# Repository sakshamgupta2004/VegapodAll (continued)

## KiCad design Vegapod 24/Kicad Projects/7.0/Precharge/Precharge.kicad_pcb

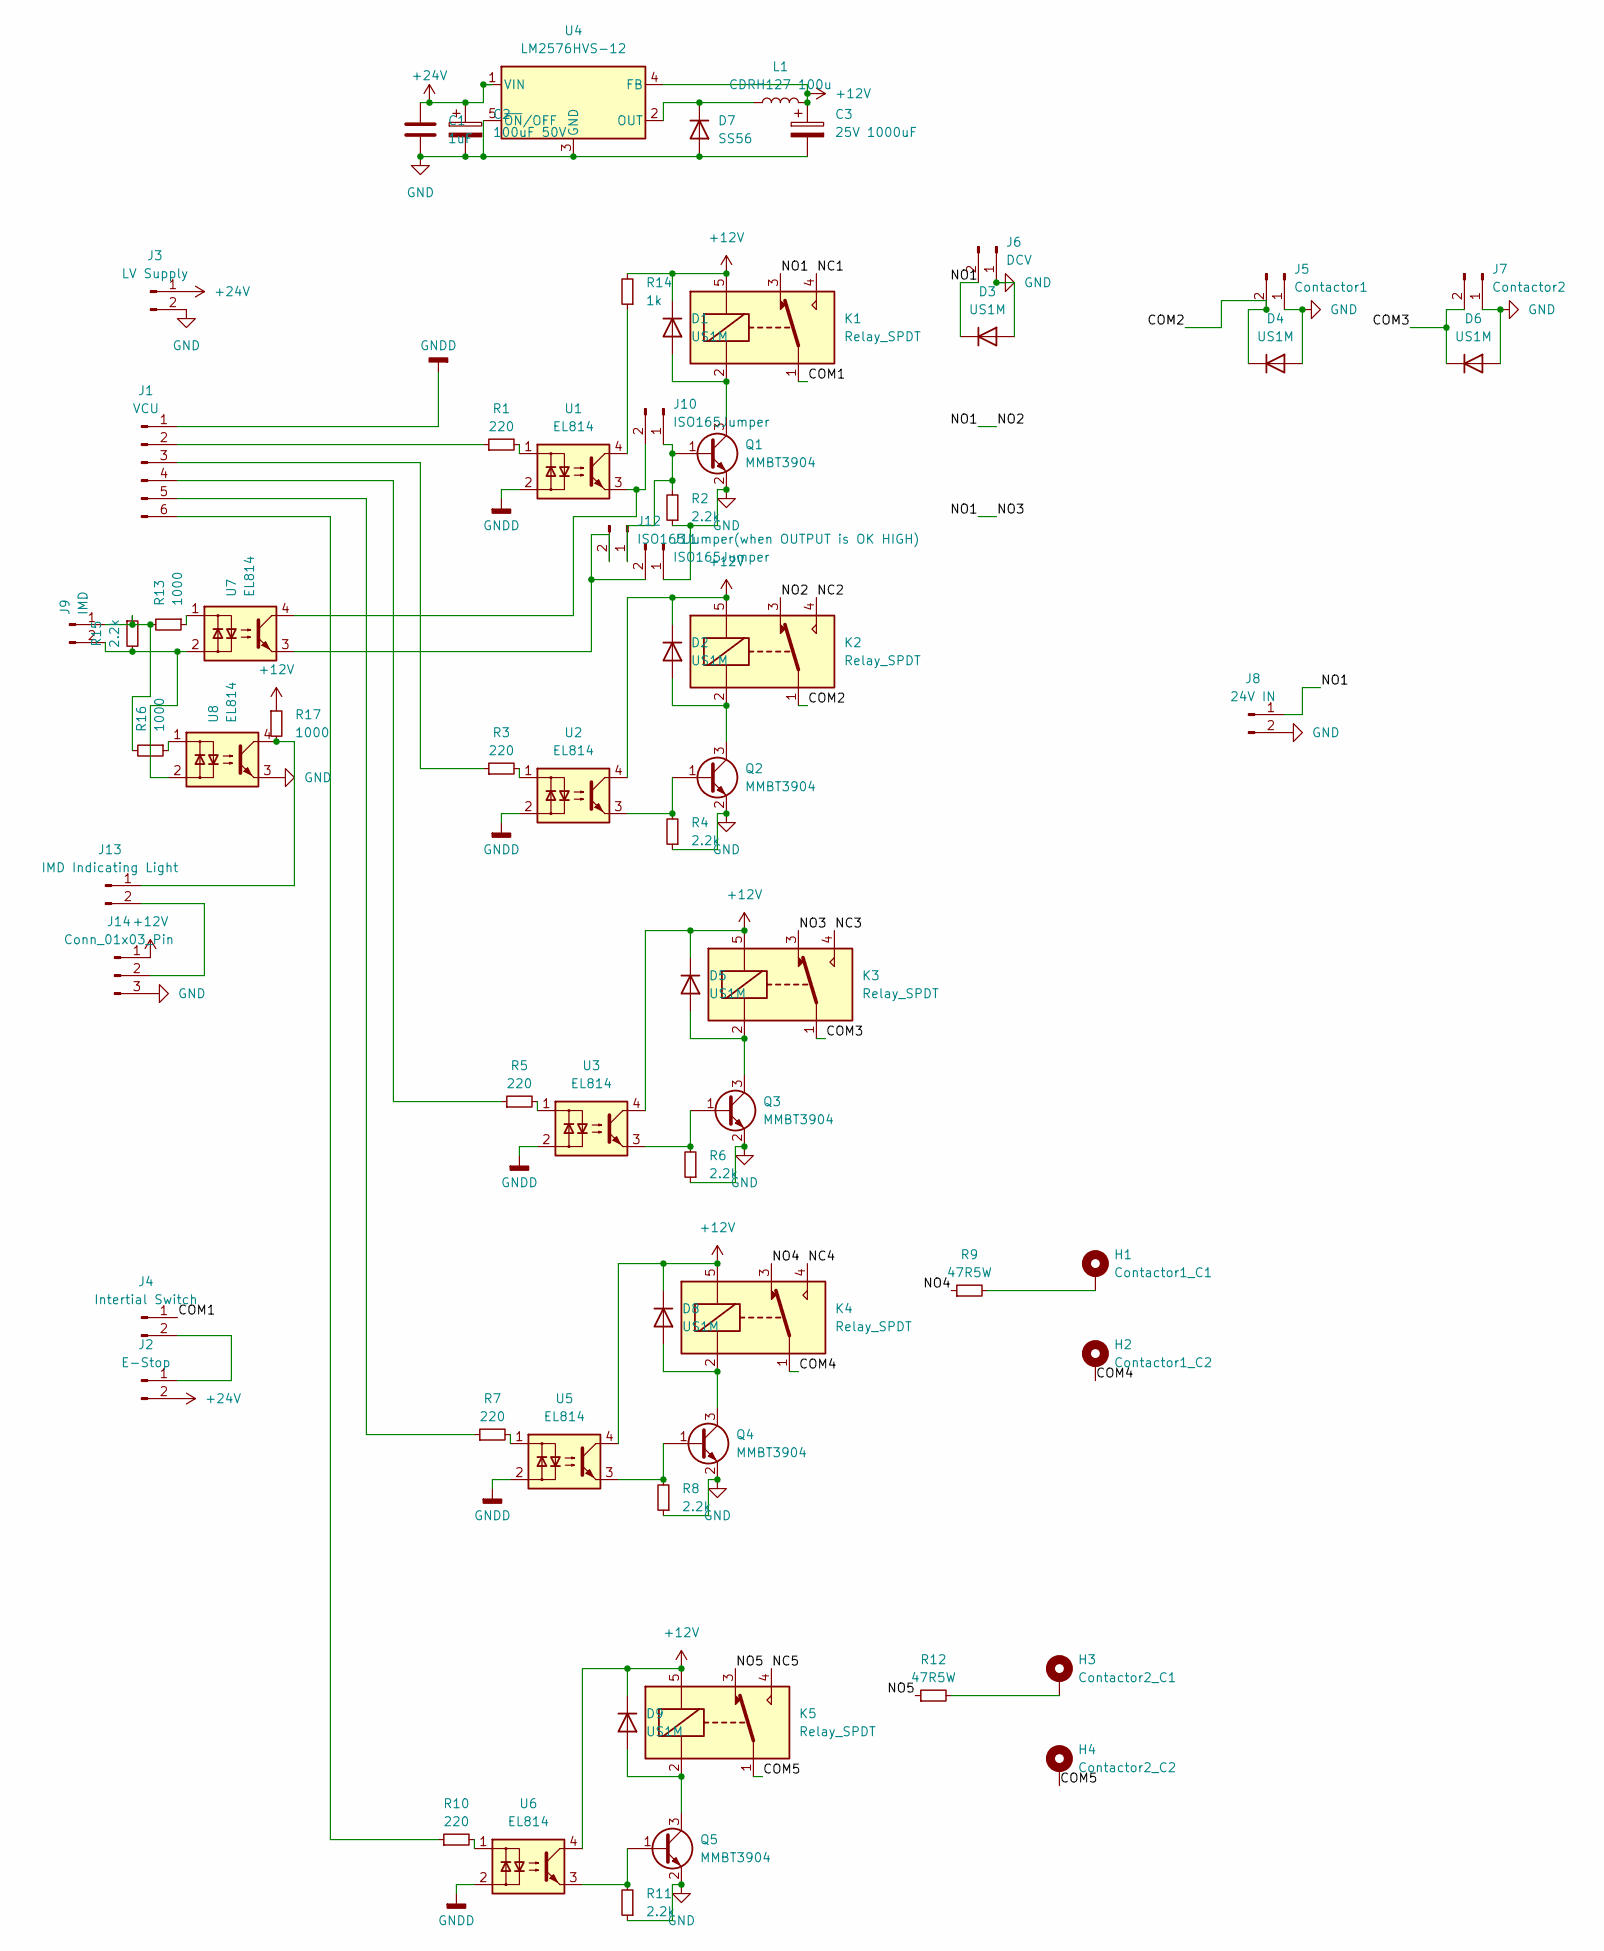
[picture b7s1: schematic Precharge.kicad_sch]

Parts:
C1: 1uF; C_1206_3216Metric_Pad1.33x1.80mm_HandSolder
C2: 100uF 50V; CP_Elec_8x10.5
C3: 25V 1000uF; CP_Elec_10x12.5
D1, D2, D3, D4, D5, D6, D8, D9: US1M; D_SMA-SMB_Universal_Handsoldering
D7: SS56; D_SMA-SMB_Universal_Handsoldering
H1: Contactor1_C1; MountingHole_6.4mm_M6_DIN965_Pad
H2: Contactor1_C2; MountingHole_6.4mm_M6_DIN965_Pad
H3: Contactor2_C1; MountingHole_6.4mm_M6_DIN965_Pad
H4: Contactor2_C2; MountingHole_6.4mm_M6_DIN965_Pad
J1: VCU; JST_XH_B6B-XH-A_1x06_P2.50mm_Vertical
J2: E-Stop; PhoenixContact_MCV_1,5_2-G-5.08_1x02_P5.08mm_Vertical
J3: LV Supply; PhoenixContact_MCV_1,5_2-G-5.08_1x02_P5.08mm_Vertical
J4: Intertial Switch; PhoenixContact_MCV_1,5_2-G-5.08_1x02_P5.08mm_Vertical
J5: Contactor1; PinHeader_1x02_P2.54mm_Vertical
J6: DCV; PhoenixContact_MCV_1,5_2-G-5.08_1x02_P5.08mm_Vertical
J7: Contactor2; PinHeader_1x02_P2.54mm_Vertical
J8: 24V IN; PinHeader_1x02_P2.54mm_Vertical
J9: IMD; PinHeader_1x02_P2.54mm_Vertical
J10, J11: ISO165Jumper; PinHeader_1x02_P1.27mm_Vertical
J12: ISO165Jumper(when OUTPUT is OK HIGH); PinHeader_1x02_P1.27mm_Vertical
J13: IMD Indicating Light; PhoenixContact_MCV_1,5_2-G-5.08_1x02_P5.08mm_Vertical
J14: Conn_01x03_Pin; PinHeader_1x03_P1.27mm_Vertical
K1, K2, K3, K4, K5: Relay_SPDT; Relay_SPDT_Omron-G5LE-1
L1: CDRH127 100u; L_12x12mm_H8mm
Q1, Q2, Q3, Q4, Q5: MMBT3904; SOT-23_Handsoldering
R1, R3, R5, R7, R10: 220; R_0805_2012Metric_Pad1.20x1.40mm_HandSolder
R2, R4, R6, R8, R11, R15: 2.2k; R_0805_2012Metric_Pad1.20x1.40mm_HandSolder
R9, R12: 47R5W; R_Axial_DIN0617_L17.0mm_D6.0mm_P7.62mm_Vertical
R13, R16, R17: 1000; R_0805_2012Metric_Pad1.20x1.40mm_HandSolder
R14: 1k; R_0805_2012Metric_Pad1.20x1.40mm_HandSolder
U1, U2, U3, U5, U6, U7, U8: EL814; SMDIP-4_W9.53mm
U4: LM2576HVS-12; TO-263-5_TabPin3

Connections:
+12V: C3.1, D1.1 (K), D2.1 (K), D5.1 (K), D8.1 (K), D9.1 (K), J14.1, K1.5, K2.5, K3.5, K4.5, K5.5, L1.2, R14.2, R17.1, U2.4, U3.4, U4.4 (FB), U5.4, U6.4
+24V: C1.1, C2.1, J2.2, J3.1, U4.1 (VIN)
/COM1: J4.1, K1.1
/COM2: D4.1 (K), J5.2, K2.1
/COM3: D6.1 (K), J7.2, K3.1
/COM4: H2.1, K4.1
/COM5: H4.1, K5.1
/NC1: K1.4
/NC2: K2.4
/NC3: K3.4
/NC4: K4.4
/NC5: K5.4
/NO1: D3.1 (K), J6.2, J8.1, K1.3, K2.3, K3.3
/NO4: K4.3, R9.1
/NO5: K5.3, R12.1
GND: C1.2, C2.2, C3.2, D3.2 (A), D4.2 (A), D6.2 (A), D7.2 (A), J3.2, J5.1, J6.1, J7.1, J8.2, J11.1, J14.3, Q1.2 (E), Q2.2 (E), Q3.2 (E), Q4.2 (E), Q5.2 (E), R2.1, R4.1, R6.1, R8.1, R11.1, U4.3 (GND), U4.5 (~ON/OFF), U8.3
GNDD: J1.1, U1.2, U2.2, U3.2, U5.2, U6.2
unnamed: D1.2 (A), K1.2, Q1.3 (C)
unnamed: D2.2 (A), K2.2, Q2.3 (C)
unnamed: D5.2 (A), K3.2, Q3.3 (C)
unnamed: D7.1 (K), L1.1, U4.2 (OUT)
unnamed: D8.2 (A), K4.2, Q4.3 (C)
unnamed: D9.2 (A), K5.2, Q5.3 (C)
unnamed: H1.1, R9.2
unnamed: H3.1, R12.2
unnamed: J1.2, R1.1
unnamed: J1.3, R3.1
unnamed: J1.4, R5.1
unnamed: J1.5, R7.1
unnamed: J1.6, R10.1
unnamed: J2.1, J4.2
unnamed: J9.1, R13.2, R15.1, R16.2
unnamed: J9.2, R15.2, U7.2, U8.2
unnamed: J10.1, J12.1, Q1.1 (B), R2.2
unnamed: J10.2, U1.3, U7.4
unnamed: J11.2, J12.2, U7.3
unnamed: J13.1, R17.2, U8.4
unnamed: J13.2, J14.2
unnamed: Q2.1 (B), R4.2, U2.3
unnamed: Q3.1 (B), R6.2, U3.3
unnamed: Q4.1 (B), R8.2, U5.3
unnamed: Q5.1 (B), R11.2, U6.3
unnamed: R1.2, U1.1
unnamed: R3.2, U2.1
unnamed: R5.2, U3.1
unnamed: R7.2, U5.1
unnamed: R10.2, U6.1
unnamed: R13.1, U7.1
unnamed: R14.1, U1.4
unnamed: R16.1, U8.1

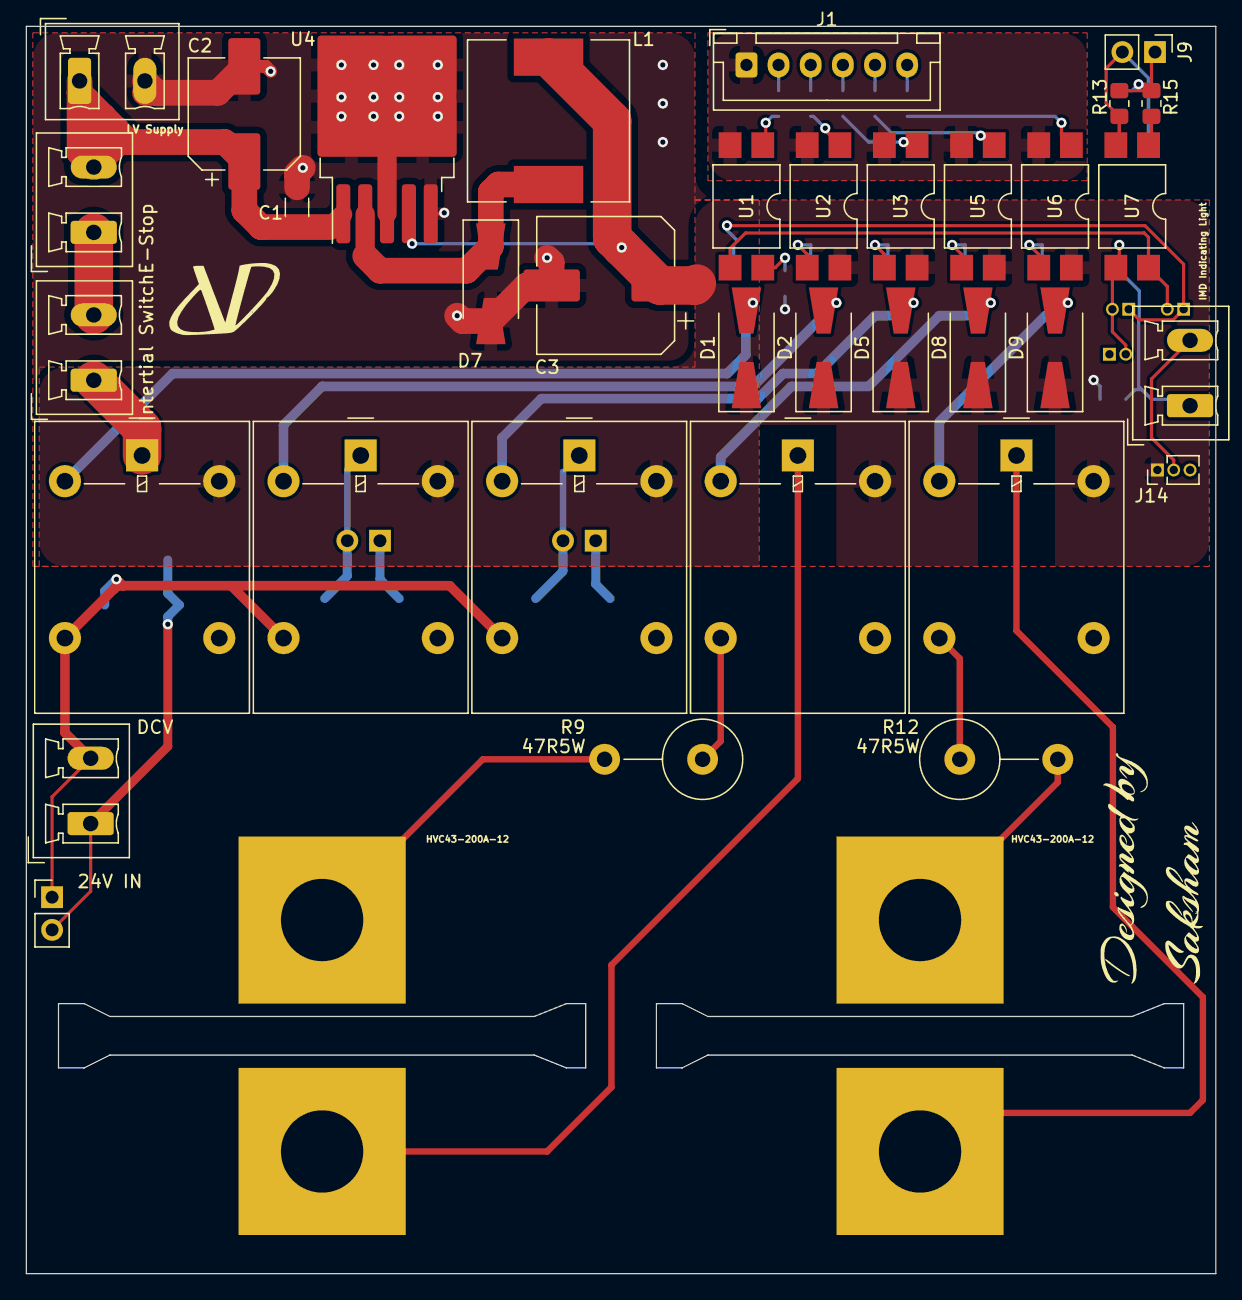
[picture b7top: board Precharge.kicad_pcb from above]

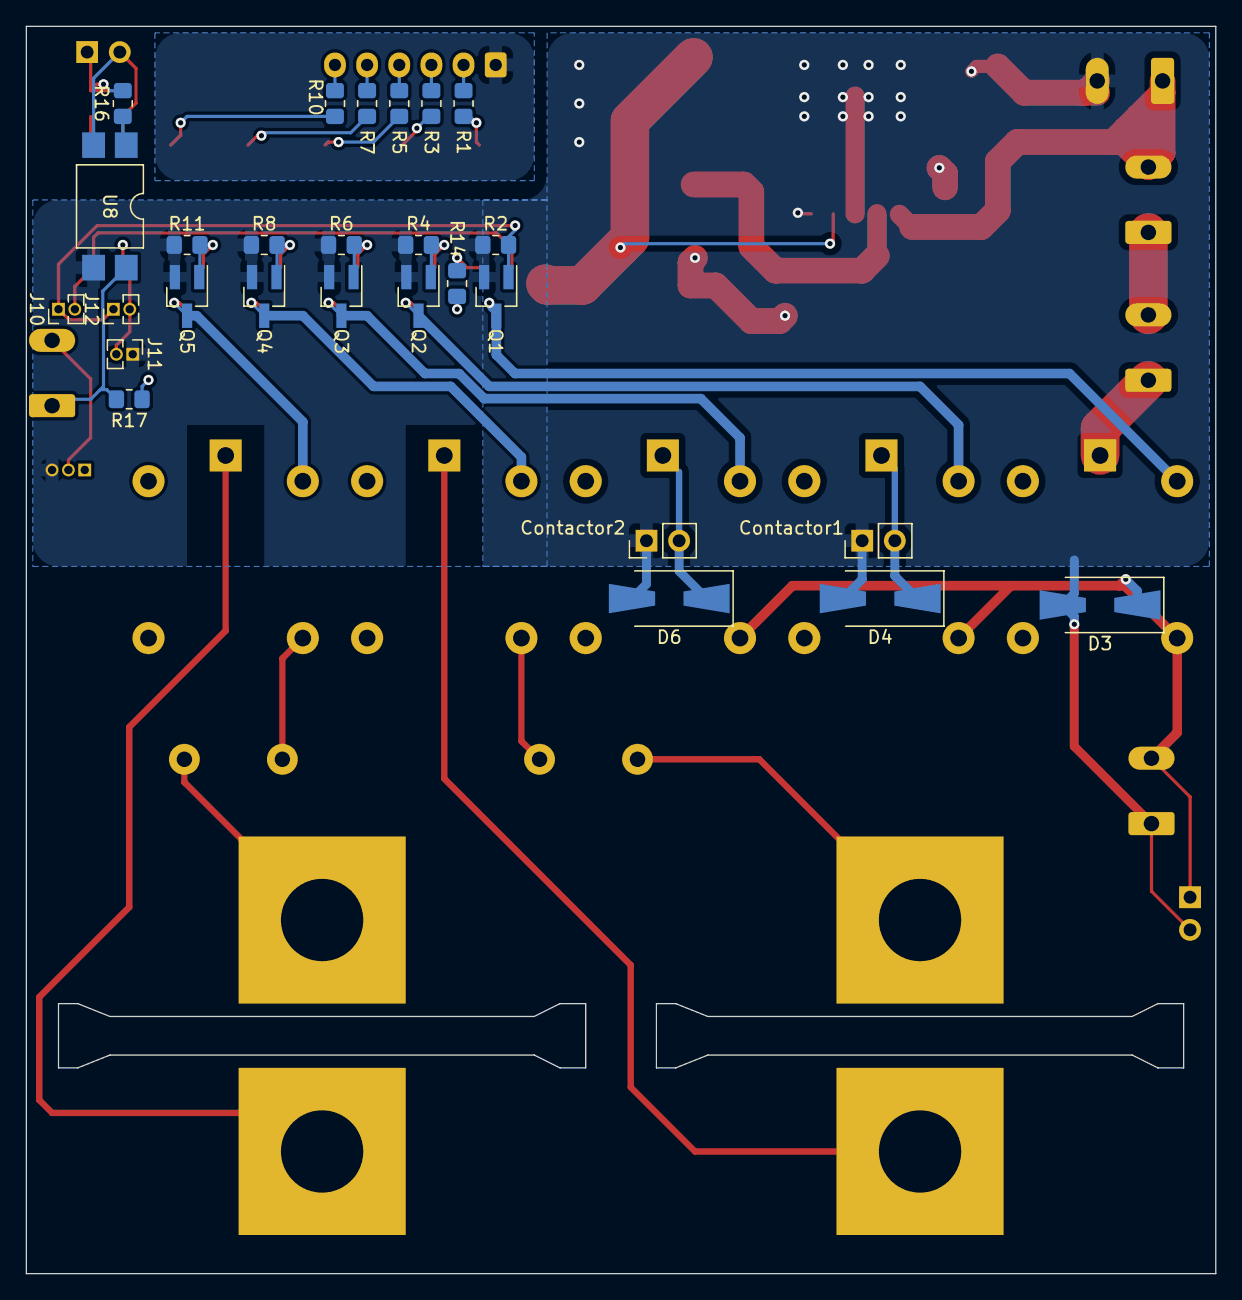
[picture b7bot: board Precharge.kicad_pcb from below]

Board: 2 copper layers, 92.5 x 97.0 mm, 66 parts (27 on the bottom side), 45 nets.

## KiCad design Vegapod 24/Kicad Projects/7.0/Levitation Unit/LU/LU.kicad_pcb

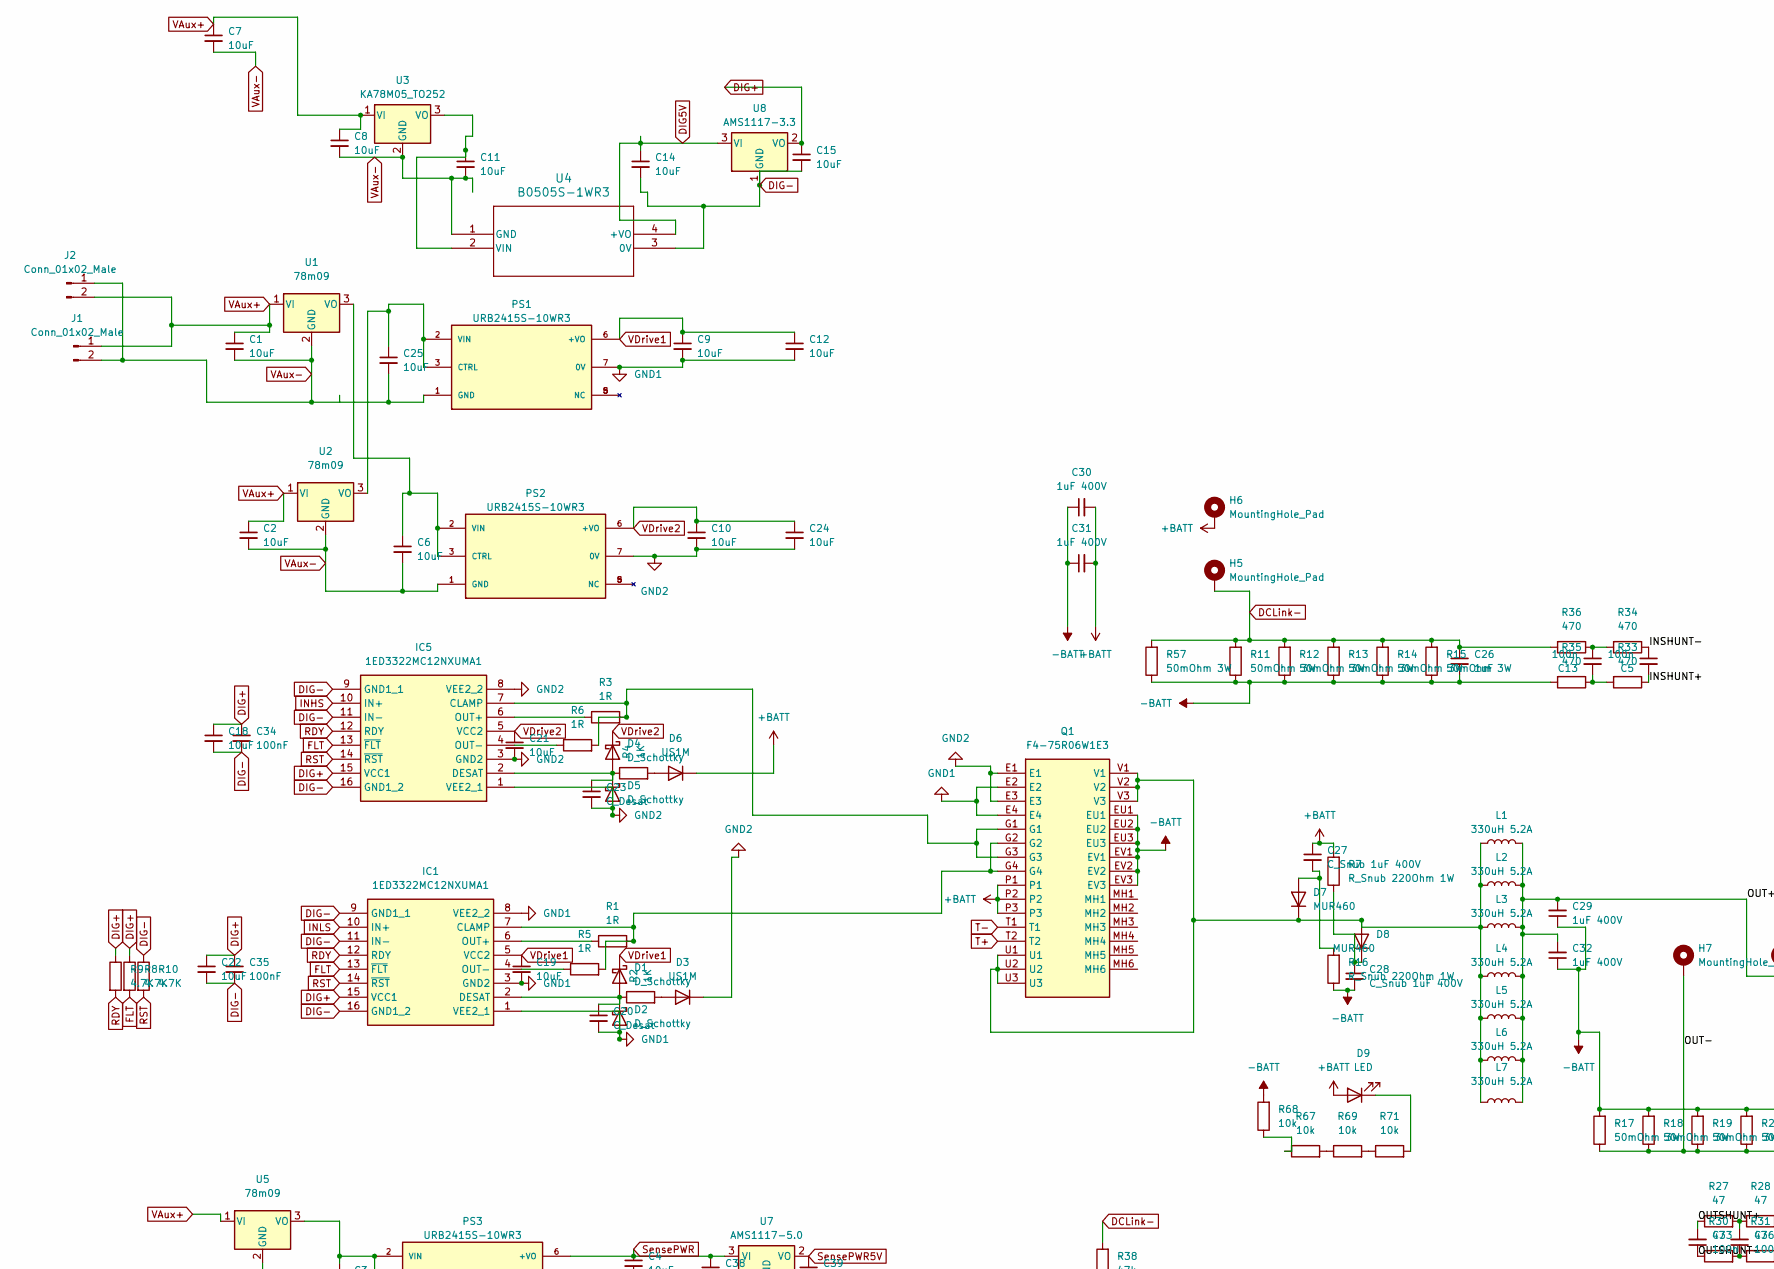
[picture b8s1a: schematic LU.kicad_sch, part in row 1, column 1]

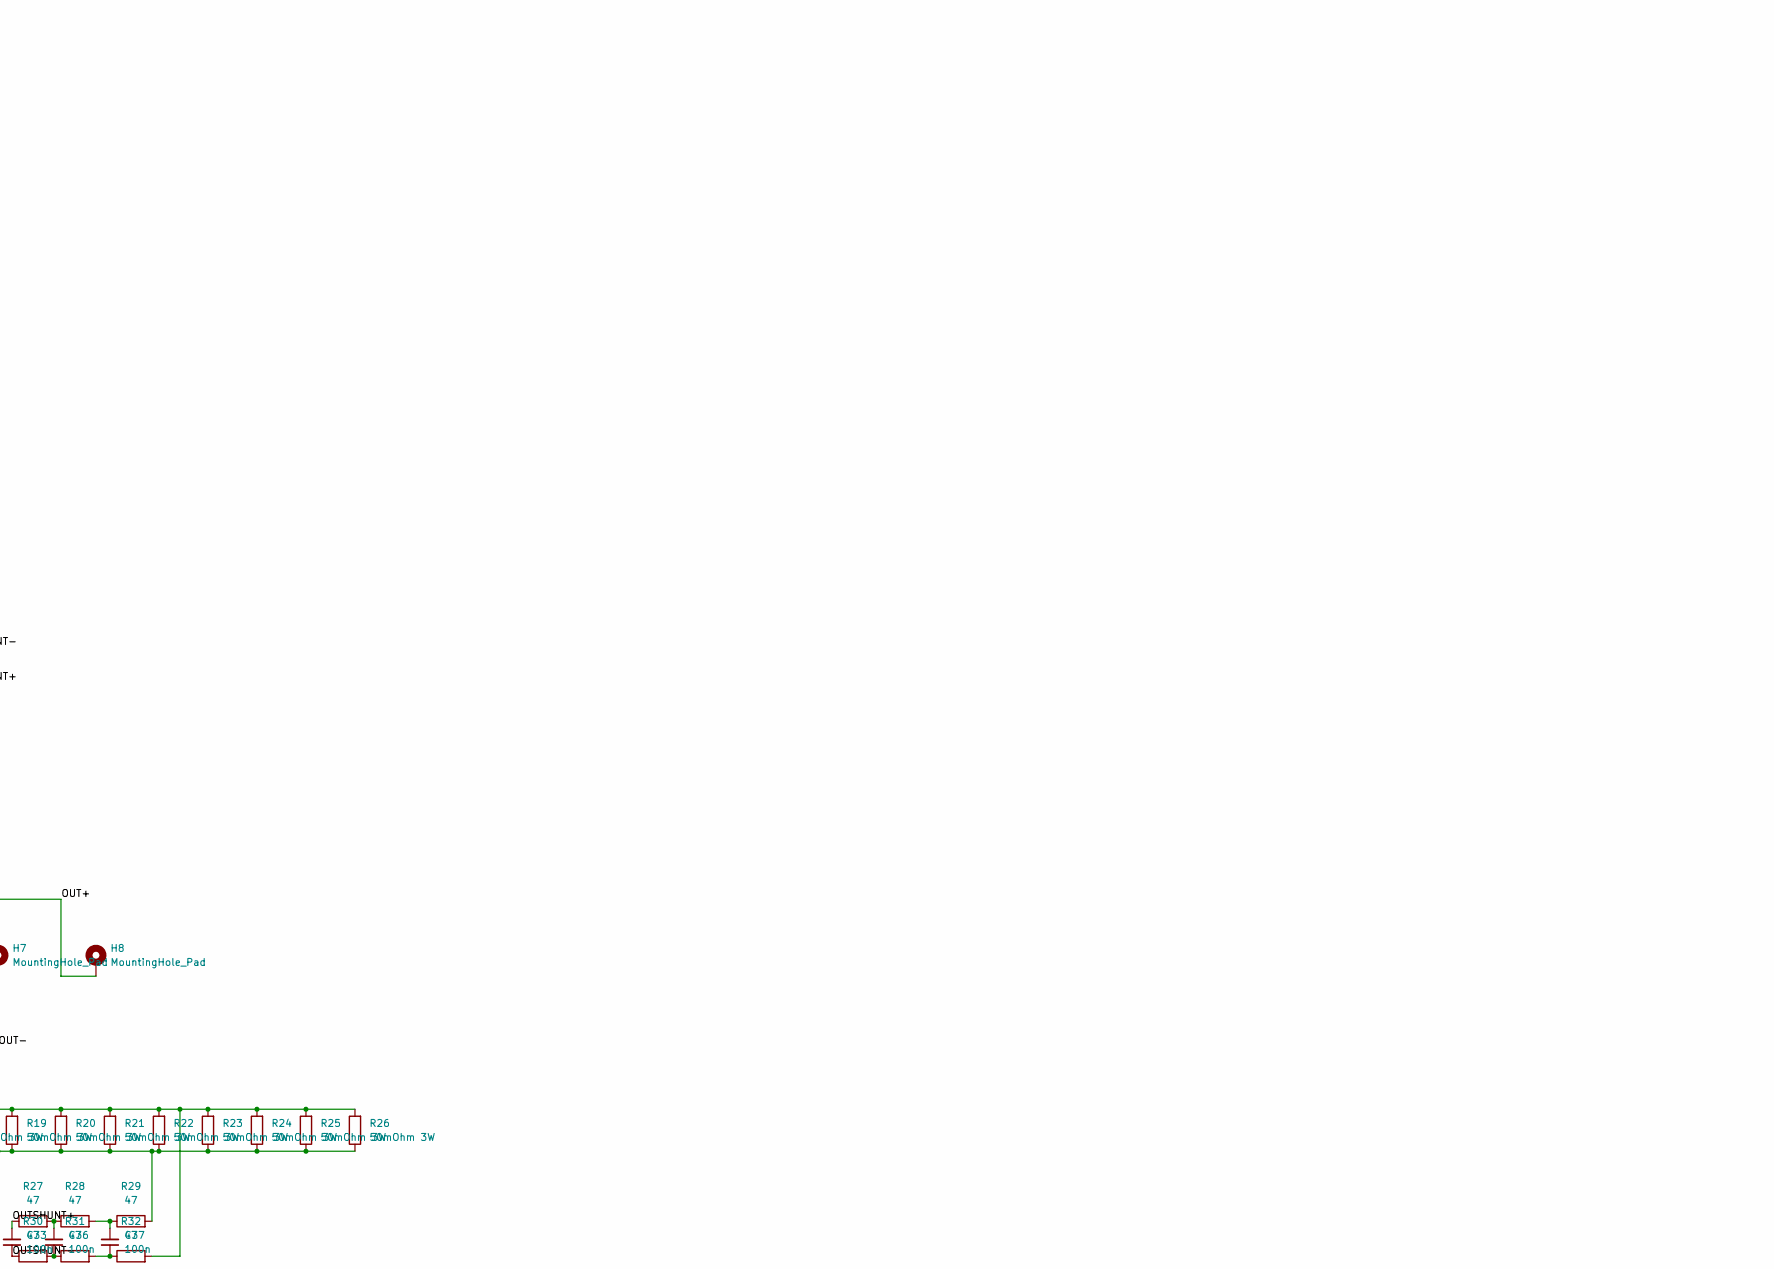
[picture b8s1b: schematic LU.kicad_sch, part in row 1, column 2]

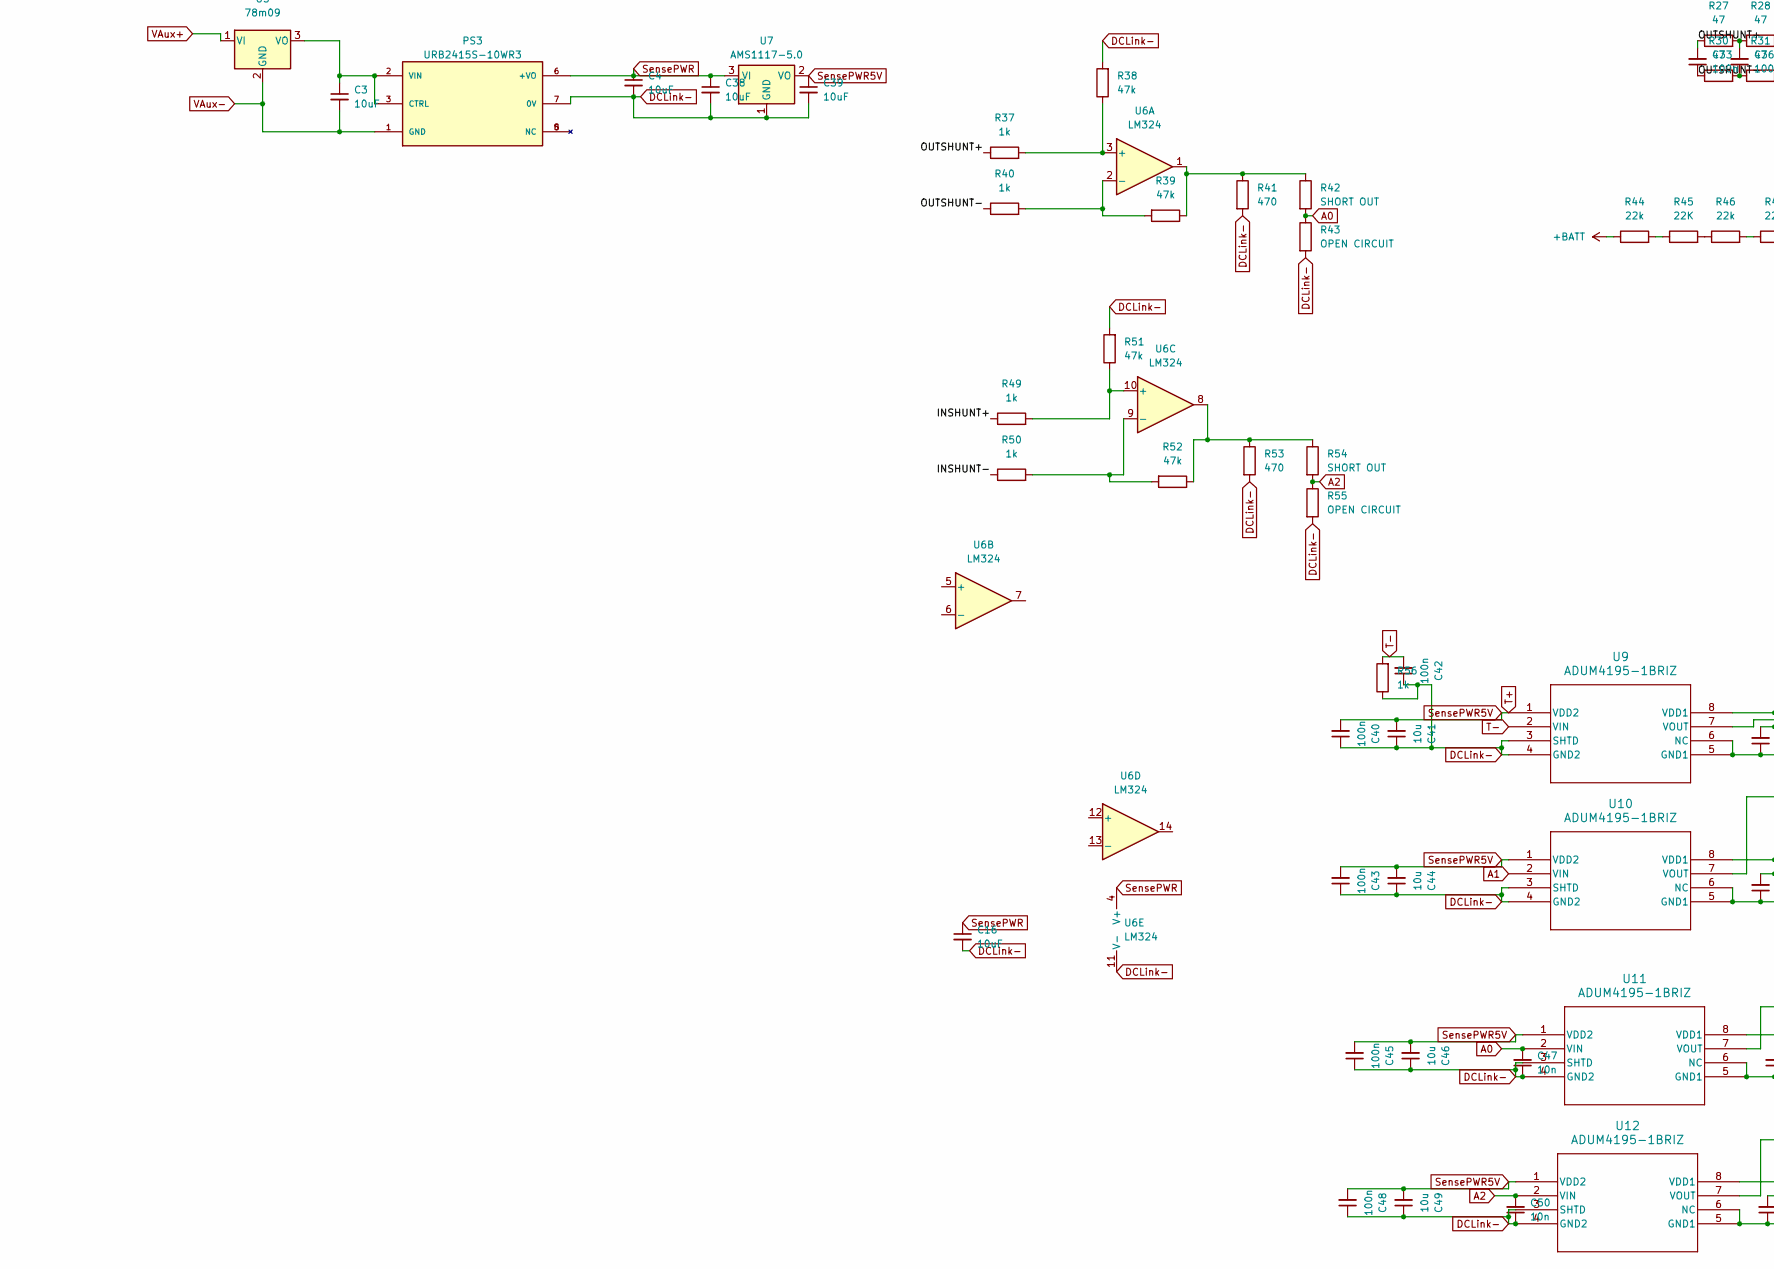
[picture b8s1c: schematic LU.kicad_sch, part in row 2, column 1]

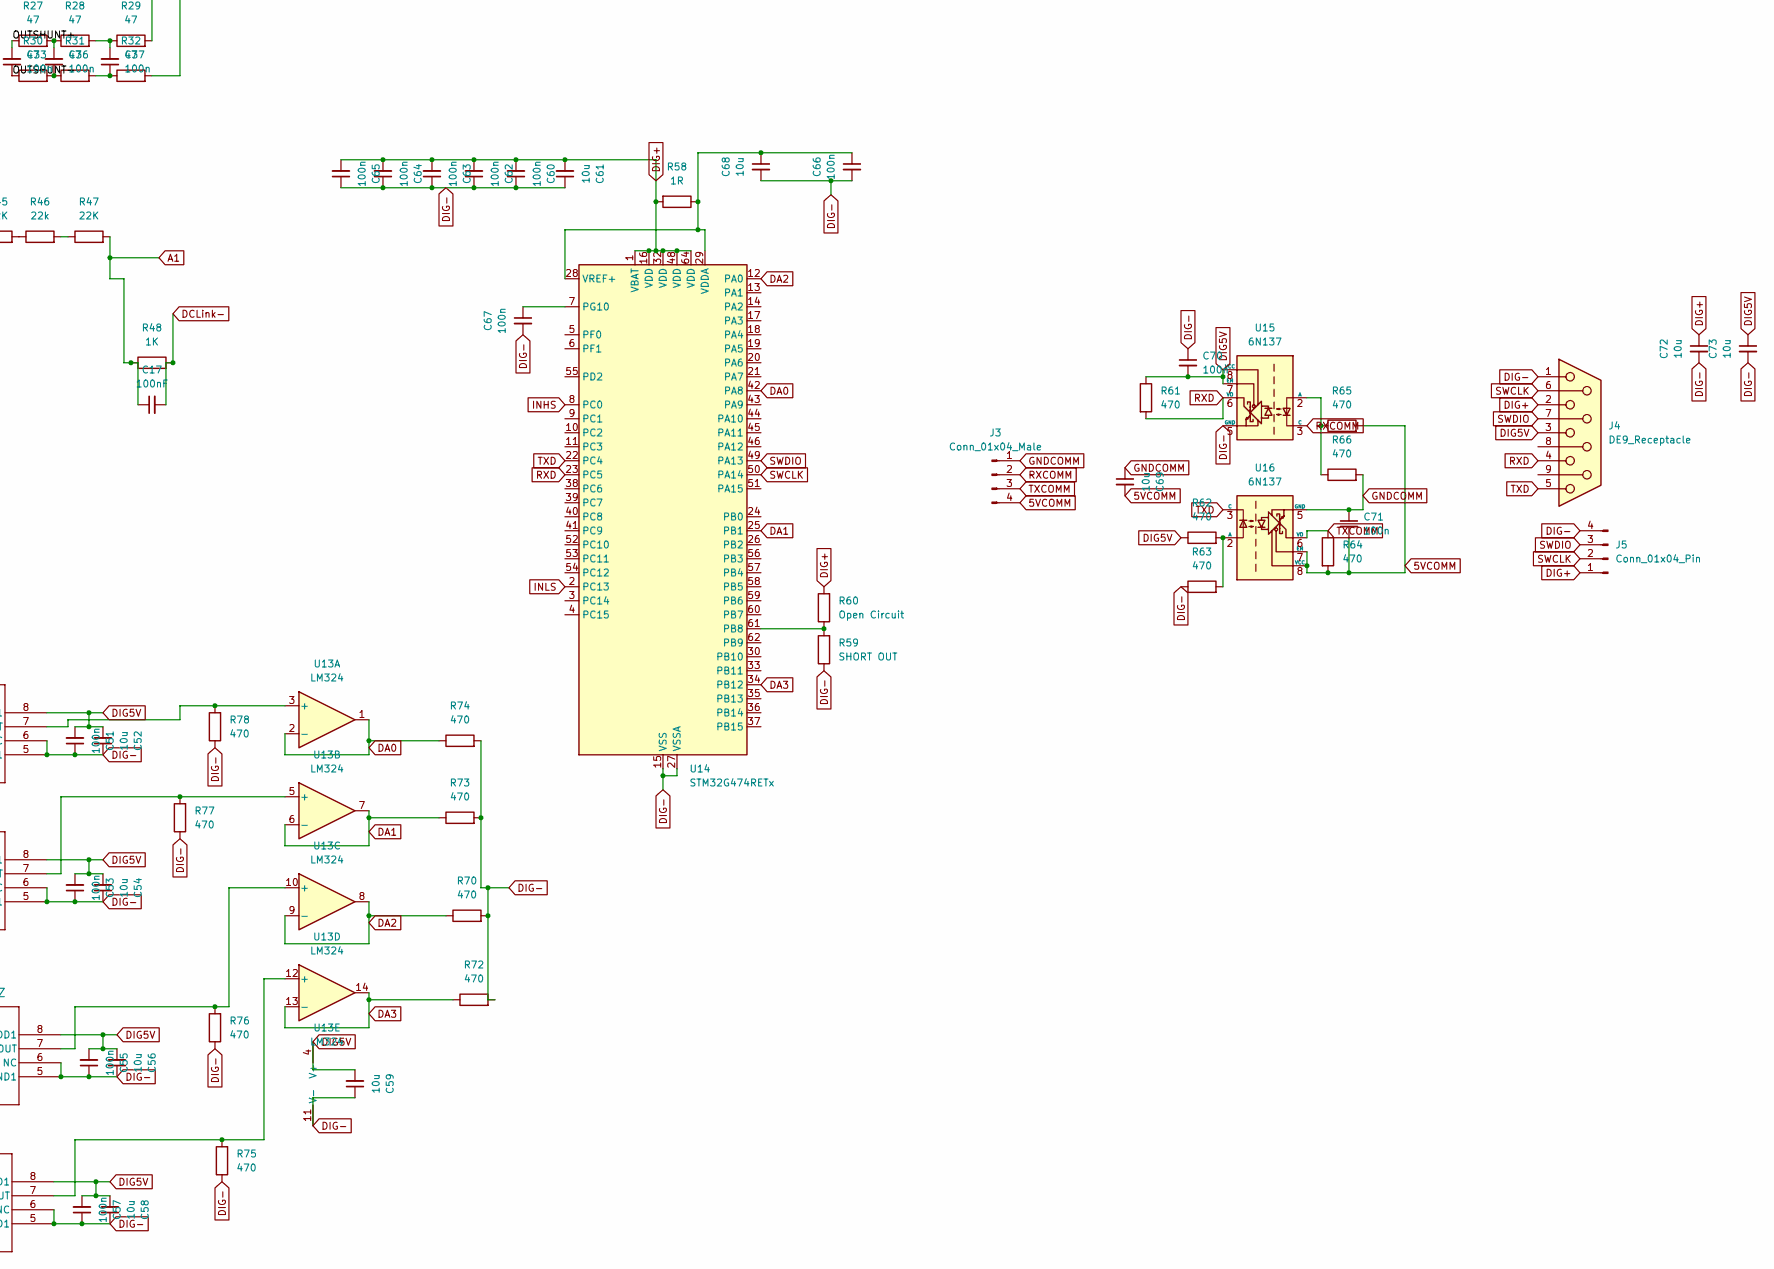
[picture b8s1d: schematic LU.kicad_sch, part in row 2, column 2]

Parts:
C1, C2, C3, C4, C6, C7, C8, C9, C10, C11, C12, C14, C15, C16, C18, C19, C21, C22, C24, C25, C38, C39: 10uF; C_1206_3216Metric_Pad1.33x1.80mm_HandSolder
C5, C13, C33, C36, C37, C40, C42, C43, C45, C48, C51, C53, C55, C57, C60, C62, C63, C64, C65, C66, C67, C70, C71: 100n; C_0805_2012Metric_Pad1.18x1.45mm_HandSolder
C17: 100nF; C_0805_2012Metric_Pad1.18x1.45mm_HandSolder
C20, C23: C_Desat; C_0603_1608Metric_Pad1.08x0.95mm_HandSolder
C26: 1uF; C_1206_3216Metric_Pad1.33x1.80mm_HandSolder
C27, C28: C_Snub 1uF 400V; C_Rect_L24.0mm_W8.3mm_P22.50mm_MKT
C29, C32: 1uF 400V; C_Rect_L19.0mm_W9.0mm_P15.00mm_MKS4
C30, C31: 1uF 400V; C_Rect_L24.0mm_W8.3mm_P22.50mm_MKT
C34, C35: 100nF; C_0603_1608Metric_Pad1.08x0.95mm_HandSolder
C41, C44, C46, C49, C52, C54, C56, C58, C59, C61, C68, C69, C72, C73: 10u; C_1206_3216Metric_Pad1.33x1.80mm_HandSolder
C47, C50: 10n; C_0805_2012Metric_Pad1.18x1.45mm_HandSolder
D1, D2, D4, D5: D_Schottky; D_SMA_Handsoldering
D3, D6: US1M; D_SMA_Handsoldering
D7, D8: MUR460; D_DO-201AE_P15.24mm_Horizontal
D9: LED; D_0805_2012Metric_Pad1.15x1.40mm_HandSolder
H5, H6: MountingHole_Pad; MountingHole_6.4mm_M6_DIN965_Pad
H7, H8: MountingHole_Pad; MountingHole_2.2mm_M2_DIN965_Pad
IC1, IC5: 1ED3322MC12NXUMA1; SOIC127P1030X265-16N; Mouser Part Number 726-1ED3322MC12NXUMA
J1: Conn_01x02_Male; JST_XH_B2B-XH-A_1x02_P2.50mm_Vertical
J2: Conn_01x02_Male; PinSocket_1x02_P2.54mm_Vertical
J3: Conn_01x04_Male; PinHeader_1x04_P2.54mm_Vertical
J4: DE9_Receptacle; DSUB-9_Male_Vertical_P2.77x2.84mm
J5: Conn_01x04_Pin; PinHeader_1x04_P1.27mm_Vertical
L1, L2, L3, L4, L5, L6, L7: 330uH 5.2A; L_Toroid_Vertical_L21.6mm_W11.4mm_P7.62mm_Pulse_KM-3
PS1, PS2, PS3: URB2415S-10WR3; CONV_URB2415S-10WR3; PARTREV 2020.11.09-A/4; DigiKey_Part_Number 2725-URB2415S-10WR3-ND
Q1: F4-75R06W1E3; F475R06W1E3; Mouser Part Number 641-F4-75R06W1E3
R1, R3, R5, R6, R58: 1R; R_0805_2012Metric_Pad1.20x1.40mm_HandSolder
R2, R4: 1K; R_0603_1608Metric_Pad0.98x0.95mm_HandSolder
R7, R16: R_Snub 220Ohm 1W; R_Box_L26.0mm_W5.0mm_P20.00mm
R8, R9, R10: 4.7K; R_0805_2012Metric_Pad1.20x1.40mm_HandSolder
R11, R12, R13, R14, R15, R17, R18, R19, R20, R21, R22, R23, R24, R25, R26, R57: 50mOhm 3W; R_2512_6332Metric_Pad1.40x3.35mm_HandSolder
R27, R28, R29, R30, R31, R32: 47; R_0805_2012Metric_Pad1.20x1.40mm_HandSolder
R33, R34, R35, R36, R41, R53, R61, R62, R63, R64, R65, R66, R70, R72, R73, R74, R75, R76, R77, R78: 470; R_0805_2012Metric_Pad1.20x1.40mm_HandSolder
R37, R40, R49, R50, R56: 1k; R_0805_2012Metric_Pad1.20x1.40mm_HandSolder
R38, R39, R51, R52: 47k; R_0805_2012Metric_Pad1.20x1.40mm_HandSolder
R42, R54: SHORT OUT; R_0805_2012Metric_Pad1.20x1.40mm_HandSolder
R43, R55: OPEN CIRCUIT; R_0805_2012Metric_Pad1.20x1.40mm_HandSolder
R44, R46: 22k; R_0805_2012Metric_Pad1.20x1.40mm_HandSolder
R45, R47: 22K; R_0805_2012Metric_Pad1.20x1.40mm_HandSolder
R48: 1K; R_0805_2012Metric_Pad1.20x1.40mm_HandSolder
R59: SHORT OUT; R_0402_1005Metric
R60: Open Circuit; R_0402_1005Metric
R67, R68, R69, R71: 10k; R_0805_2012Metric_Pad1.20x1.40mm_HandSolder
U1, U2, U5: 78m09; TO-252-2
U3: KA78M05_TO252; TO-252-2
U4: B0505S-1WR3; B0505S_MNS
U6, U13: LM324; SOIC-14_3.9x8.7mm_P1.27mm
U7: AMS1117-5.0; SOT-223-3_TabPin2
U8: AMS1117-3.3; SOT-223-3_TabPin2
U9, U10, U11, U12: ADUM4195-1BRIZ; RI-8-1_ADI
U14: STM32G474RETx; LQFP-64_10x10mm_P0.5mm
U15, U16: 6N137; SSO-8_6.7x9.8mm_P2.54mm_Clearance8mm

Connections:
5VCOMM: C69.2, C71.2, J3.4, R64.2, R65.2, U16.7 (EN), U16.8 (VCC)
+BATT: C27.1, C30.2, C31.2, D6.1 (K), D9.2 (A), H6.1, Q1.P1, Q1.P2, Q1.P3, R7.2, R44.1
-BATT: C26.2, C28.2, C29.1, C30.1, C31.1, C32.1, Q1.EU1, Q1.EU2, Q1.EU3, Q1.EV1, Q1.EV2, Q1.EV3, R11.1, R12.1, R13.1, R14.1, R15.1, R16.1, R17.2, R18.2, R19.2, R20.2, R21.2, R22.2, R23.2, R24.2, R25.2, R26.2, R32.2, R35.2, R57.1, R68.2
/INSHUNT+: C5.2, R33.1, R49.1
/INSHUNT-: C5.1, R34.1, R50.1
/OUT+: C29.2, C32.2, H8.1, L1.2, L2.2, L3.2, L4.2, L5.2, L6.2, L7.2
/OUT-: H7.1, R17.1, R18.1, R19.1, R20.1, R21.1, R22.1, R23.1, R24.1, R25.1, R26.1, R29.2
/OUTSHUNT+: C33.2, R27.1, R37.1
/OUTSHUNT-: C33.1, R30.1, R40.1
A0: C47.2, R42.2, R43.1, U11.2 (VIN)
A1: C17.1, R47.2, R48.1, U10.2 (VIN)
A2: C50.2, R54.2, R55.1, U12.2 (VIN)
DA0: R74.1, U13.1, U13.2 (-), U14.42 (PA8)
DA1: R73.1, U13.6 (-), U13.7, U14.25 (PB1)
DA2: R70.1, U13.8, U13.9 (-), U14.12 (PA0)
DA3: R72.1, U13.13 (-), U13.14, U14.34 (PB12)
DCLink-: C4.2, C16.2, C17.2, C26.1, C38.2, C39.2, C40.1, C41.1, C42.1, C43.1, C44.1, C45.1, C46.1, C47.1, C48.1, C49.1, C50.1, H5.1, PS3.7 (0V), R11.2, R12.2, R13.2, R14.2, R15.2, R36.2, R38.2, R41.2, R43.2, R48.2, R51.2, R53.2, R55.2, R56.1, R57.2, U6.11 (V-), U7.1 (GND), U9.3 (SHTD), U9.4 (GND2), U10.3 (SHTD), U10.4 (GND2), U11.3 (SHTD), U11.4 (GND2), U12.3 (SHTD), U12.4 (GND2)
DIG5V: C14.1, C51.2, C52.2, C53.2, C54.2, C55.2, C56.2, C57.2, C58.2, C59.2, C70.2, C73.1, J4.3, R61.1, R62.1, U4.4 (+VO), U8.3 (VI), U9.8 (VDD1), U10.8 (VDD1), U11.8 (VDD1), U12.8 (VDD1), U13.4 (V+), U15.7 (EN), U15.8 (VCC)
DIG+: C15.1, C18.1, C22.1, C34.1, C35.1, C60.2, C61.2, C62.2, C63.2, C64.2, C65.2, C72.1, IC1.15 (VCC1), IC5.15 (VCC1), J4.2, J5.1, R8.1, R9.1, R58.2, R60.2, U8.2 (VO), U14.1 (VBAT), U14.16 (VDD), U14.32 (VDD), U14.48 (VDD), U14.64 (VDD)
DIG-: C14.2, C15.2, C18.2, C22.2, C34.2, C35.2, C51.1, C52.1, C53.1, C54.1, C55.1, C56.1, C57.1, C58.1, C59.1, C60.1, C61.1, C62.1, C63.1, C64.1, C65.1, C66.2, C67.2, C68.2, C70.1, C72.2, C73.2, IC1.9 (GND1_1), IC1.11 (IN-), IC1.16 (GND1_2), IC5.9 (GND1_1), IC5.11 (IN-), IC5.16 (GND1_2), J4.1, J5.4, R10.1, R59.1, R63.1, R70.2, R72.2, R73.2, R74.2, R75.1, R76.1, R77.1, R78.1, U4.3 (0V), U8.1 (GND), U9.5 (GND1), U9.6 (NC), U10.5 (GND1), U10.6 (NC), U11.5 (GND1), U11.6 (NC), U12.5 (GND1), U12.6 (NC), U13.11 (V-), U14.15 (VSS), U14.27 (VSSA), U14.31 (VSS), U14.47 (VSS), U14.63 (VSS), U15.5 (GND)
FLT: IC1.13 (~FLT), IC5.13 (~FLT), R8.2
GND1: C9.2, C12.2, C19.2, C20.2, D2.2 (A), IC1.1 (VEE2_1), IC1.3 (GND2), IC1.8 (VEE2_2), PS1.7 (0V), Q1.E2, Q1.E4
GND2: C10.2, C21.2, C23.2, C24.2, D3.1 (K), D5.2 (A), IC5.1 (VEE2_1), IC5.3 (GND2), IC5.8 (VEE2_2), PS2.7 (0V), Q1.E1, Q1.E3
GNDCOMM: C69.1, C71.1, J3.1, R66.2, U16.5 (GND)
INHS: IC5.10 (IN+), U14.8 (PC0)
INLS: IC1.10 (IN+), U14.2 (PC13)
unnamed: C13.1, R34.2, R36.1
unnamed: C13.2, R33.2, R35.1
unnamed: C36.1, R30.2, R31.1
unnamed: C36.2, R27.2, R28.1
unnamed: C37.1, R31.2, R32.1
unnamed: C37.2, R28.2, R29.1
unnamed: C20.1, D1.2 (A), D2.1 (K), IC1.2 (DESAT), R2.1
unnamed: D3.2 (A), R2.2
unnamed: C23.1, D4.2 (A), D5.1 (K), IC5.2 (DESAT), R4.1
unnamed: D6.2 (A), R4.2
unnamed: C27.2, D7.2 (A), R16.2
unnamed: D7.1 (K), D8.2 (A), L1.1, L2.1, L3.1, L4.1, L5.1, L6.1, L7.1, Q1.U1, Q1.U2, Q1.U3, Q1.V1, Q1.V2, Q1.V3
unnamed: C28.1, D8.1 (K), R7.1
unnamed: D9.1 (K), R71.2
unnamed: IC1.7 (CLAMP), Q1.G2, Q1.G4, R1.2, R5.2
unnamed: IC1.6 (OUT+), R1.1
unnamed: IC1.4 (OUT-), R5.1
unnamed: IC5.7 (CLAMP), Q1.G1, Q1.G3, R3.2, R6.2
unnamed: IC5.6 (OUT+), R3.1
unnamed: IC5.4 (OUT-), R6.1
unnamed: C25.1, PS1.2 (VIN), PS1.3 (CTRL), U2.3 (VO)
unnamed: C6.1, PS2.2 (VIN), PS2.3 (CTRL), U1.3 (VO)
unnamed: C3.1, PS3.2 (VIN), PS3.3 (CTRL), U5.3 (VO)
unnamed: R39.1, R41.1, R42.1, U6.1
unnamed: R44.2, R45.1
unnamed: R45.2, R46.1
unnamed: R46.2, R47.1
unnamed: R52.1, R53.1, R54.1, U6.8
unnamed: R67.1, R68.1
unnamed: R67.2, R69.1
unnamed: R69.2, R71.1
unnamed: C11.1, U3.3 (VO), U4.2 (VIN)
unnamed: R37.2, R38.1, U6.3 (+)
unnamed: R39.2, R40.2, U6.2 (-)
unnamed: R49.2, R51.1, U6.10 (+)
unnamed: R50.2, R52.2, U6.9 (-)
unnamed: R77.2, U10.7 (VOUT), U13.5 (+)
unnamed: R76.2, U11.7 (VOUT), U13.10 (+)
unnamed: R75.2, U12.7 (VOUT), U13.12 (+)
unnamed: R78.2, U9.7 (VOUT), U13.3 (+)
unnamed: R59.2, R60.1, U14.61 (PB8)
unnamed: C67.1, U14.7 (PG10)
unnamed: C66.1, C68.1, R58.1, U14.28 (VREF+), U14.29 (VDDA)
unnamed: R65.1, R66.1, U15.2 (A)
unnamed: R62.2, R63.2, U16.2 (A)
RDY: IC1.12 (RDY), IC5.12 (RDY), R9.2
RST: IC1.14 (~RST), IC5.14 (~RST), R10.2
RXCOMM: J3.2, U15.3 (C)
RXD: J4.4, R61.2, U14.23 (PC5), U15.6 (VO)
SWCLK: J4.6, J5.2, U14.50 (PA14)
SWDIO: J4.7, J5.3, U14.49 (PA13)
SensePWR: C4.1, C16.1, C38.1, PS3.6 (+VO), U6.4 (V+), U7.3 (VI)
SensePWR5V: C39.1, C40.2, C41.2, C43.2, C44.2, C45.2, C46.2, C48.2, C49.2, Q1.T2, U7.2 (VO), U9.1 (VDD2), U10.1 (VDD2), U11.1 (VDD2), U12.1 (VDD2)
T-: C42.2, Q1.T1, R56.2, U9.2 (VIN)
TXCOMM: J3.3, R64.1, U16.6 (VO)
TXD: J4.5, U14.22 (PC4), U16.3 (C)
VAux+: C1.1, C2.1, C7.1, C8.1, J1.1, J2.2, U1.1 (VI), U2.1 (VI), U3.1 (VI), U5.1 (VI)
VAux-: C1.2, C2.2, C3.2, C6.2, C7.2, C8.2, C11.2, C25.2, J1.2, J2.1, PS1.1 (GND), PS2.1 (GND), PS3.1 (GND), U1.2 (GND), U2.2 (GND), U3.2 (GND), U4.1 (GND), U5.2 (GND)
VDrive1: C9.1, C12.1, C19.1, D1.1 (K), IC1.5 (VCC2), PS1.6 (+VO)
VDrive2: C10.1, C21.1, C24.1, D4.1 (K), IC5.5 (VCC2), PS2.6 (+VO)
